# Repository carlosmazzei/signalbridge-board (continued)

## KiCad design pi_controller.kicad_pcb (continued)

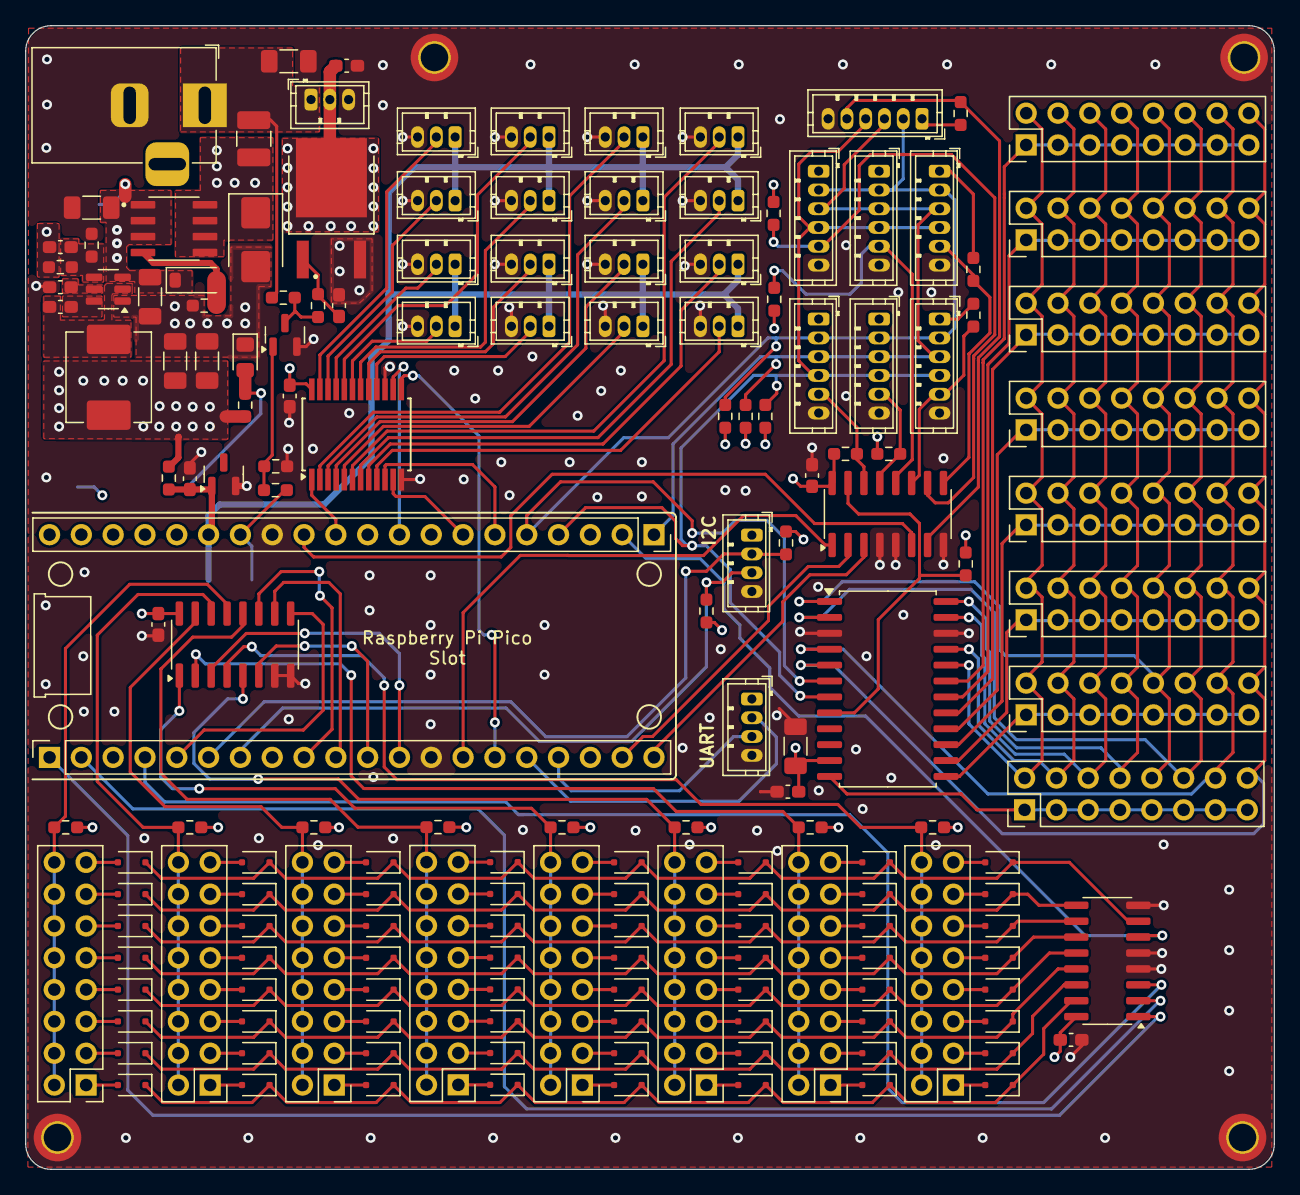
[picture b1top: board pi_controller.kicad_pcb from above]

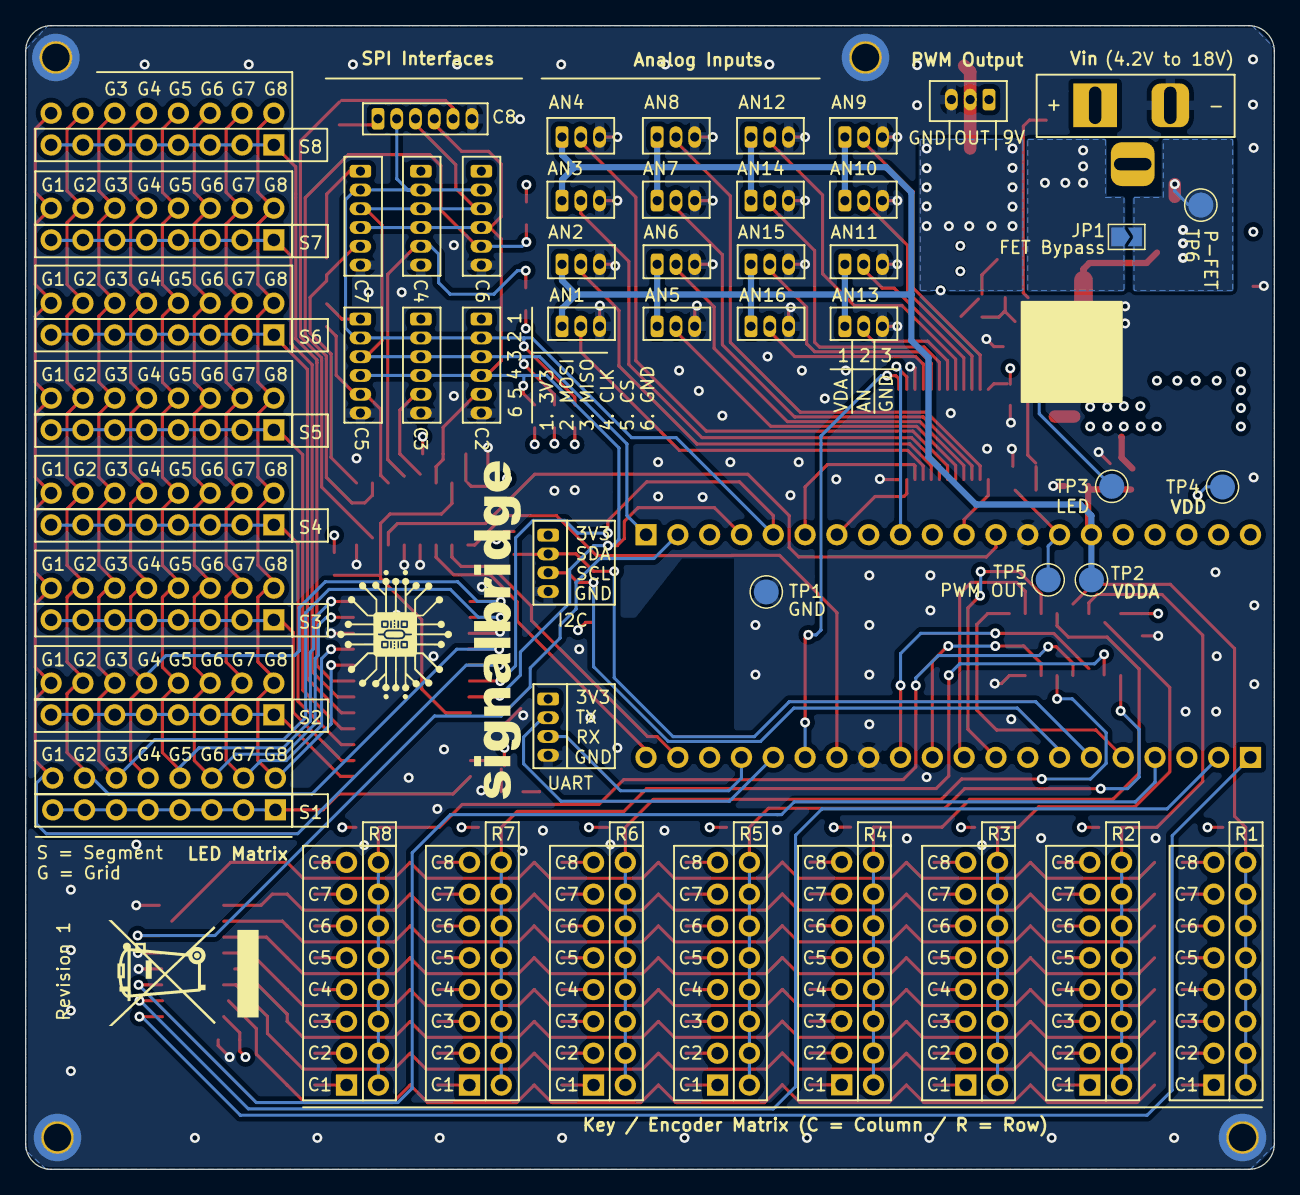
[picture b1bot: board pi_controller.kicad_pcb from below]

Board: 4 copper layers, 99.7 x 91.3 mm, 182 parts (7 on the bottom side), 162 nets.

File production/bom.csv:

"Designator","Comment","Footprint","Qty","LCSC PN","Package","Power","Tolerance","Voltage Rating","Temperature Rating","Saturation Current","Checked"
"AN1,AN2,AN3,AN4,AN5,AN6,AN7,AN8,AN9,AN10,AN11,AN12,AN13,AN14,AN15,AN16","-- mixed values --","PiMatrix:JST_ZH_B3B-ZR_1x03_P1.50mm_Vertical_SilkSafe","16","C495558","","","","","","",""
"C1,C9,C11,C12,C13","0.1uF","Capacitor_SMD:C_0603_1608Metric_Pad1.08x0.95mm_HandSolder","5","C14663","0603","","-- mixed values --","50V","","",""
"C2,C3","22uF","Capacitor_SMD:C_1206_3216Metric_Pad1.33x1.80mm_HandSolder","2","C12891","1206","","10%","25V","X5R","",""
"C4","10uF","Capacitor_SMD:C_1206_3216Metric_Pad1.33x1.80mm_HandSolder","1","C13585","1206","","10%","50V","X5R","",""
"C5","470nF","Capacitor_SMD:C_0603_1608Metric_Pad1.08x0.95mm_HandSolder","1","C1623","0603","","10%","25V","X7R","",""
"C6","220nF","Capacitor_SMD:C_0603_1608Metric_Pad1.08x0.95mm_HandSolder","1","C21120","0603","","10%","25V","","",""
"C7","100pF","Capacitor_SMD:C_0603_1608Metric_Pad1.08x0.95mm_HandSolder","1","C14858","0603","","10%","50V","","",""
"C8","2.2uF","Capacitor_SMD:C_0603_1608Metric_Pad1.08x0.95mm_HandSolder","1","C23630","0603","","10%","16V","","",""
"C10","100uF","Capacitor_SMD:C_1206_3216Metric_Pad1.33x1.80mm_HandSolder","1","C15008","1206","","10%","50V","","",""
"C14","1nF","Capacitor_SMD:C_0603_1608Metric_Pad1.08x0.95mm_HandSolder","1","C1588","0603","","10%","50V","X7R","",""
"C15","47uF","Capacitor_SMD:C_1206_3216Metric_Pad1.33x1.80mm_HandSolder","1","C76659","1206","","10%","50V","","",""
"D1","LED","LED_SMD:LED_0805_2012Metric_Pad1.15x1.40mm_HandSolder","1","C2297","0805","","","","","",""
"D2,D3,D4,D5,D6,D7,D8,D9,D10,D11,D12,D13,D14,D15,D16,D17,D18,D19,D20,D21,D22,D23,D24,D25,D26,D27,D28,D29,D30,D31,D32,D33,D34,D35,D36,D37,D38,D39,D40,D41,D42,D43,D44,D45,D46,D47,D48,D49,D50,D51,D52,D53,D54,D55,D56,D57,D58,D59,D60,D61,D62,D63,D64,D65","BAT54J","Diode_SMD:D_SOD-323F","64","C358488","","","","","","",""
"J1","PWM","Connector_PinHeader_2.54mm:PinHeader_1x03_P2.54mm_Vertical","1","C49257","","","","","","",""
"J2","DC Supply","Connector_BarrelJack:BarrelJack_Horizontal","1","C381116","","","","","","",""
"J26,J27,J28,J29,J32,J33,J34,J35,JR1,JR2,JR3,JR4,JR5,JR6,JR7,JR8","-- mixed values --","Connector_PinHeader_2.54mm:PinHeader_2x08_P2.54mm_Vertical","16","C779499","","","","","","",""
"J30,J31","-- mixed values --","PiMatrix:JST_ZH_B4B-ZR_1x04_P1.50mm_Vertical_SilkSafe","2","C163034","","","","","","",""
"JSPI1,JSPI2,JSPI3,JSPI4,JSPI5,JSPI6,JSPI7","Conn_01x06","PiMatrix:JST_ZH_B6B-ZR_1x06_P1.50mm_Vertical_SilkSafe","7","C495631","","","","","","",""
"L1","3.3uH","Inductor_SMD:L_Sunlord_MWSA0604S","1","C5189747","","","20%","","","6.5A",""
"Q1","AOD4184A","AOD4184A:DPAK228P994X240-4N","1","C99124","","","","","","",""
"Q2","MMBT3904","Package_TO_SOT_SMD:SOT-23","1","C20526","","","","","","",""
"R1,R5","10k","Resistor_SMD:R_0603_1608Metric_Pad0.98x0.95mm_HandSolder","2","C25804","0603","100mW","1%","","","",""
"R2","33.2k","Resistor_SMD:R_0603_1608Metric_Pad0.98x0.95mm_HandSolder","1","C23003","0603","100mW","1%","","","",""
"R3","1.5k","Resistor_SMD:R_0603_1608Metric_Pad0.98x0.95mm_HandSolder","1","C543357","0603","250mW","1%","","","",""
"R4","330R","Resistor_SMD:R_0603_1608Metric_Pad0.98x0.95mm_HandSolder","1","C23138","0603","100mW","1%","","","",""
"R6","47R","Resistor_SMD:R_0603_1608Metric_Pad0.98x0.95mm_HandSolder","1","C23182","0603","100mW","1%","","","",""
"R7,R8,R17","2.2k","Resistor_SMD:R_0603_1608Metric_Pad0.98x0.95mm_HandSolder","3","C4190","0603","100mW","1%","","","",""
"R9,R10,R11,R12,R13,R14,R15,R16","3.3k","Resistor_SMD:R_0603_1608Metric_Pad0.98x0.95mm_HandSolder","8","C22978","0603","100mW","1%","","","",""
"R18","10R","Resistor_SMD:R_0603_1608Metric_Pad0.98x0.95mm_HandSolder","1","C22859","0603","100mW","1%","","","",""
"TP1,TP2,TP3,TP4","TestPoint","TestPoint:TestPoint_Pad_D4.0mm","4","","","","","","","",""
"U1","AP62300TWU","Package_TO_SOT_SMD:TSOT-23-6","1","C1883519","","","","","","",""
"U2","CD74HC4067SM96","Package_SO:SSOP-24_5.3x8.2mm_P0.65mm","1","C98457","","","","","","",""
"U3","LM4040DBZ-3","Package_TO_SOT_SMD:SOT-23","1","C460608","","","","","","",""
"U5,U7","74HC138","Package_SO:SOIC-16_3.9x9.9mm_P1.27mm","2","C6818","","","","","","",""
"U6","TM1639 (TA2009B)","Package_SO:SOP-24_7.5x15.4mm_P1.27mm","1","C20611984","","","","","","",""

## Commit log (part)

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2025-03-03 Edit git ignore
2025-03-03 Removing DS_Store
2025-03-03 Adjust readme format
2025-03-05 Update layout and rules
2025-03-08 Update routing
2025-03-08 Minor adjustments
2025-03-08 Component repositioning to compact form factor
2025-03-09 Adjusting DRC checks
2025-03-09 Update PCB footprints
2025-03-09 Created gerber for quote and updated layout
2025-03-09 Adjusting component placement to have more room
2025-03-10 Layout ground pour and other adjustments
2025-03-10 Refining layout
2025-03-11 Improving PWM circuit
2025-03-11 Adjusting components
2025-03-13 New connectos and adjusted component spacing
2025-03-18 Adjusting footprints for production
2025-03-19 Changing 10R resistor
2025-07-20 Project name change to signalbridge and board final revision
2025-07-21 Changed part number (out of stock)
2025-07-26 Created the slot for the pi and udpated silk screen
2025-08-02 Adjusting testpoint pads and adding 74hc4051 datasheet
2025-08-18 Bump actions/checkout from 4 to 5
    Bumps [actions/checkout](https://github.com/actions/checkout) from 4 to 5.
    - [Release notes](https://github.com/actions/checkout/releases)
    - [Changelog](https://github.com/actions/checkout/blob/main/CHANGELOG.md)
    - [Commits](https://github.com/actions/checkout/compare/v4...v5)
    ---
    updated-dependencies:
2025-11-24 Bump actions/checkout from 5 to 6
    Bumps [actions/checkout](https://github.com/actions/checkout) from 5 to 6.
    - [Release notes](https://github.com/actions/checkout/releases)
    - [Changelog](https://github.com/actions/checkout/blob/main/CHANGELOG.md)
    - [Commits](https://github.com/actions/checkout/compare/v5...v6)
    ---
    updated-dependencies:
2026-01-01 Upgrading power supply protection
2026-01-05 Adding power supply protection, ground pour in the top and new 3d models
2026-02-01 Adjusting DRC setting
2026-02-01 Add exclude from BOM to testpoint
2026-02-01 Updating images and BOM for JP1
2026-02-01 Updating production files
2026-04-13 Bump softprops/action-gh-release from 2 to 3
    Bumps [softprops/action-gh-release](https://github.com/softprops/action-gh-release) from 2 to 3.
    - [Release notes](https://github.com/softprops/action-gh-release/releases)
    - [Changelog](https://github.com/softprops/action-gh-release/blob/master/CHANGELOG.md)
    - [Commits](https://github.com/softprops/action-gh-release/compare/v2...v3)
    ---
    updated-dependencies:
2026-04-21 chore: consolidate datasheets into a single lowercase folder
    Merge the uppercase Datasheets/ (12 PDFs) into the lowercase datasheets/
    (3 PDFs). The two folders contained disjoint files and were not tracked
    by any code or workflow path; consolidating avoids the case collision
    that is fragile on macOS/Windows and puts every component datasheet in
    one discoverable location.
2026-04-21 docs: move PRODUCTION_CHECKLIST into docs/ and document project layout
    Move PRODUCTION_CHECKLIST.md into a new docs/ folder so long-form docs
    stop accumulating at the root while README.md and LICENSE stay where
    GitHub surfaces them from. Add a Project Structure section to README.md
    that describes what each top-level folder contains and calls out the
    folder names that the KiCad library tables and the release workflow
    depend on, so future contributors do not rename them accidentally.
2026-04-21 docs: correct license reference in README (CERN-OHL, not MIT)
    The README body text claimed MIT, but the LICENSE file and the badge
    at the top of the README are both CERN Open Hardware Licence. Align
    the body text with the actual license.
2026-04-21 docs: remove emojis from README
    https://claude.ai/code/session_01L3z4iiXhmfee4zYUDBgtyC
2026-06-22 Bump actions/checkout from 6 to 7
    Bumps [actions/checkout](https://github.com/actions/checkout) from 6 to 7.
    - [Release notes](https://github.com/actions/checkout/releases)
    - [Changelog](https://github.com/actions/checkout/blob/main/CHANGELOG.md)
    - [Commits](https://github.com/actions/checkout/compare/v6...v7)
    ---
    updated-dependencies:
